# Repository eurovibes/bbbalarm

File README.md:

<!-- SPDX-FileCopyrightText: 2021 Benedikt Spranger <b.spranger@linutronix.de> -->
<!-- SPDX-License-Identifier: CERN-OHL-S-2.0 -->

# bbbalarm - An Alarm cape for Beaglebone Black

The Beaglobone Black is a TI Sitara AM3359 ARM Cortex-A8 CPU based
evaluation board with two 40pin 100mil pinsockets. These pinsockets
can be used for additional functionality boards called capes.
The bbbalarm cape enhance the Beaglebone Black by adding coupled and
decoupled inputs, that can be used to supervise an air condition or read out
a presence detector.

## License rules

bbbalarm is provided under the terms of the CERN-OHL-S license version 2 as
provided in the LICENSES/CERN-OHL-S-2.0 file.

Instead of adding license boilerplates to the individual files, bbbalarm uses
SPDX license identifiers, which are machine parseable and considered legaly
equivalent.

The SPDX license identifier in bbbalarm shall be added at the first possible
line in a file which can contain a comment. This is normally the first line
except for scripts. Scripts require the #!PATH_TO_INTERPRETER tag in the
first line; place the SPDX identifier into the second line.

The SPDX license identifier is added in form of a comment.

## Copyright and License

Copyright Benedikt Spranger 2021.
This source describes Open Hardware and is licensed under the CERNOHL-S v2.
You may redistribute and modify this source and make products using it
under the terms of the CERN-OHL-S v2
(https://ohwr.org/cern ohl s v2.txt ).
This source is distributed WITHOUT ANY EXPRESS OR IMPLIED
WARRANTY, INCLUDING OF MERCHANTABILITY, SATISFACTORY
QUALITY AND FITNESS FOR A PARTICULAR PURPOSE. Please see
the CERN-OHL-S v2 for applicable conditions.
Source location: https://github.com/eurovibes/bbbalarm
As per CERN-OHL-S v2 section 4, should You produce hardware based
on this source, You must where practicable maintain the Source Location
visible on the external case of the bbbalarm or other products you make using
this source.

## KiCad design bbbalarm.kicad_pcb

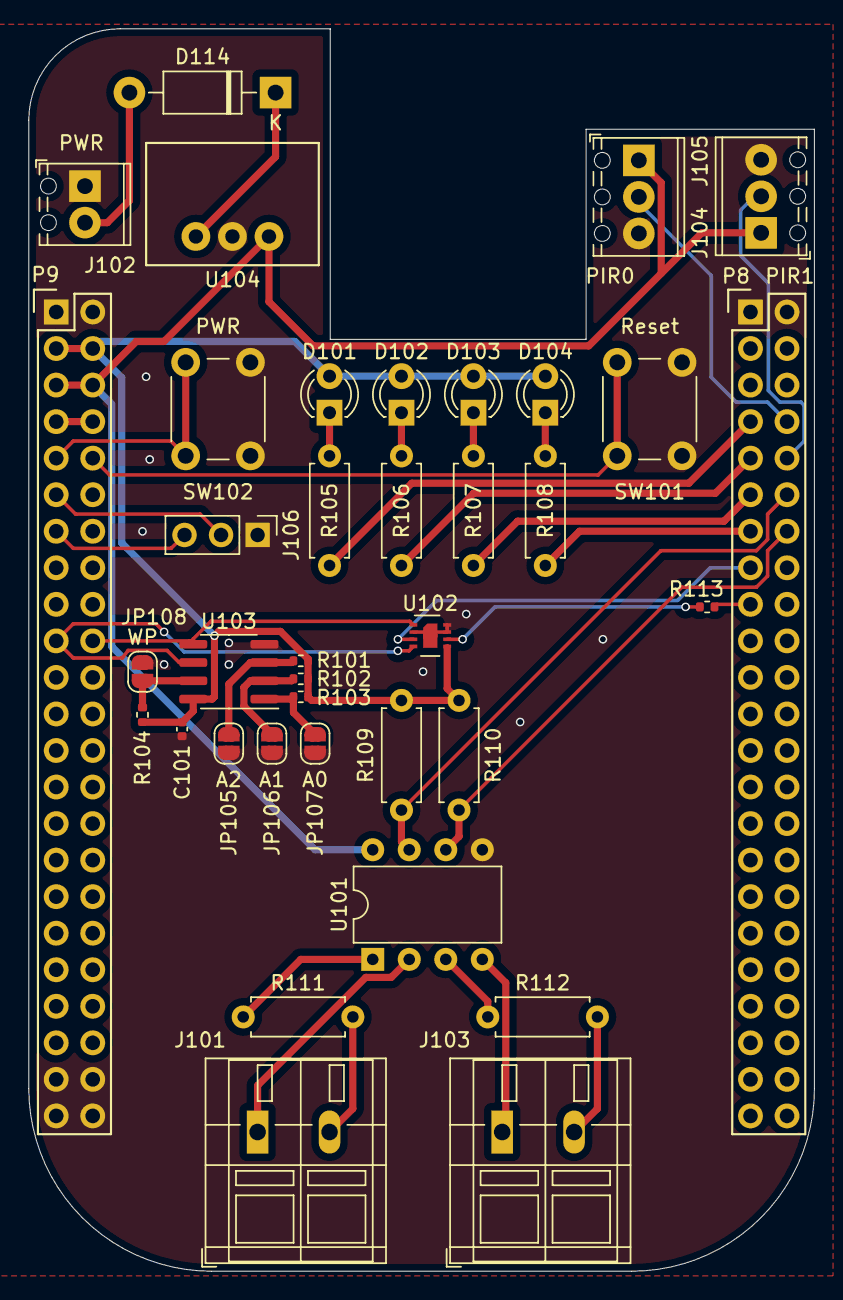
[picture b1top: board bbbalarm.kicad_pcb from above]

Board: 2 copper layers, 54.6 x 86.4 mm, 37 parts (0 on the bottom side), 37 nets.

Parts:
C101: 100n; C_0402_1005Metric
D101, D102, D103, D104: LED; LED_D3.0mm
D114: 1N4004; D_DO-41_SOD81_P10.16mm_Horizontal
J101: IN0; TerminalBlock_WAGO_236-102_1x02_P5.00mm_45Degree
J102: PWR; TerminalBlock_Phoenix_MPT-0,5-2-2.54_1x02_P2.54mm_Horizontal
J103: IN1; TerminalBlock_WAGO_236-102_1x02_P5.00mm_45Degree
J104: PIR0; TerminalBlock_Phoenix_MPT-0,5-3-2.54_1x03_P2.54mm_Horizontal
J105: PIR1; TerminalBlock_Phoenix_MPT-0,5-3-2.54_1x03_P2.54mm_Horizontal
J106: serial; PinHeader_1x03_P2.54mm_Vertical
JP105: A2; SolderJumper-2_P1.3mm_Open_RoundedPad1.0x1.5mm
JP106: A1; SolderJumper-2_P1.3mm_Open_RoundedPad1.0x1.5mm
JP107: A0; SolderJumper-2_P1.3mm_Open_RoundedPad1.0x1.5mm
JP108: WP; SolderJumper-2_P1.3mm_Open_RoundedPad1.0x1.5mm
P8, P9: BeagleBone_Black_Header; Socket_BeagleBone_Black
R101, R102, R103, R104, R113: 1k; R_0402_1005Metric
R105, R106, R107, R108, R109, R110: 1k; R_Axial_DIN0207_L6.3mm_D2.5mm_P7.62mm_Horizontal
R111, R112: 330; R_Axial_DIN0207_L6.3mm_D2.5mm_P7.62mm_Horizontal
SW101: Reset; SW_PUSH_6mm
SW102: PWR; SW_PUSH_6mm
U101: HCPL-263N; DIP-8_W7.62mm
U102: SHT35-DIS; Sensirion_DFN-8-1EP_2.5x2.5mm_P0.5mm_EP1.1x1.7mm
U103: AT24C512C-SSHD-T; SOIC-8_3.9x4.9mm_P1.27mm
U104: WPMDH1100xx1S

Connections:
+3V3: C101.1, D101.2 (A), D102.2 (A), D103.2 (A), D104.2 (A), P9.3, P9.4, R101.1, R102.1, R103.1, R104.1, R109.1, R110.1, U102.5 (VDD), U103.8 (VCC)
+5V: J104.1, J105.1, P9.5, P9.6, U101.8 (VCC), U104.3 (Vout)
/ALERT: P8.15, U102.3 (ALERT)
/IN0: P8.12, R109.2, U101.7 (VO1)
/IN1: P8.14, R110.2, U101.6 (VO2)
/LED0: P8.7, R105.2
/LED1: P8.9, R106.2
/LED2: P8.11, R107.2
/LED3: P8.13, R108.2
/PIR0: J104.2, P8.8
/PIR1: J105.2, P8.10
/RX: J106.2, P9.11
/SCL: P9.19, U102.4 (SCL), U103.6 (SCL)
/SDA: P9.20, U102.1 (SDA), U103.5 (SDA)
/TX: J106.3, P9.13
/nRST: P8.17, R113.1
GNDD: C101.2, J102.1, J104.3, J105.3, J106.1, JP105.2 (B), JP106.2 (B), JP107.2 (B), JP108.2 (B), P8.1, P8.2, P9.1, P9.2, P9.43, P9.44, P9.45, P9.46, SW101.2, SW102.2, U101.5 (GND), U102.2 (ADDR), U102.7 (R), U102.8 (VSS), U102.9 (VSS), U103.4 (GND), U104.2 (GND)
unnamed: D101.1 (K), R105.1
unnamed: D102.1 (K), R106.1
unnamed: D103.1 (K), R107.1
unnamed: D104.1 (K), R108.1
unnamed: D114.1 (K), U104.1 (Vin)
unnamed: D114.2 (A), J102.2
unnamed: J101.1, U101.2 (C1)
unnamed: J101.2, R111.2
unnamed: J103.1, U101.4 (A2)
unnamed: J103.2, R112.2
unnamed: JP105.1 (A), R101.2, U103.3 (A2)
unnamed: JP106.1 (A), R102.2, U103.2 (A1)
unnamed: JP107.1 (A), R103.2, U103.1 (A0)
unnamed: JP108.1 (A), R104.2, U103.7 (WP)
unnamed: R111.1, U101.1 (A1)
unnamed: R112.1, U101.3 (C2)
unnamed: R113.2, U102.6 (~RESET)
PWR_BUT: P9.9, SW102.1
SYS_5V: P9.7, P9.8
SYS_RESETN: P9.10, SW101.1

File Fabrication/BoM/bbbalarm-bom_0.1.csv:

Row,Referencias,Parte,Valor,P/N,Fabricante,Cod. Digi-Key,Footprint,Descripción,Quantity Per PCB
1,C101,C,100 nF,,,,C_0402_1005Metric,,1
2,D114,1N4004,1N4004,,,,D_DO-41_SOD81_P10.16mm_Horizontal,,1
3,D101 D102 D103 D104,LED,LED,,,,LED_D3.0mm,,4
4,J101 J102 J103,Conn_01x02,IN0,,,,TerminalBlock_WAGO_236-102_1x02_P5.00mm_45Degree,,3
5,J104 J105,Conn_01x03,PIR0,,,,"TerminalBlock_Phoenix_MPT-0,5-3-2.54_1x03_P2.54mm_Horizontal",,2
6,JP105 JP106 JP107 JP108,Jumper_NO_Small,A2,,,,SolderJumper-2_P1.3mm_Open_RoundedPad1.0x1.5mm,,4
7,P8 P9,Conn_02x23_Odd_Even,BeagleBone_Black_Header,,,,Socket_BeagleBone_Black,,2
8,R101 R102 R103 R104 R105 R106 R107 R108 R109 R110 R111 R112,R,1 kΩ,,,,R_0402_1005Metric,,12
9,SW101 SW102,SW_Push_45deg,Reset,,,,SW_PUSH_6mm,,2
10,U103,AT24CS64-SSHM,AT24C512C-SSHD-T,,,,SOIC-8_3.9x4.9mm_P1.27mm,,1
11,U101,HCPL-263N,HCPL-263N,,,,DIP-8_W7.62mm,,1
12,U104,WPMDH1100xx1S,WPMDH1100xx1S,,,,WPMDH1100xx1S,,1





Project info:
Schematic:,bbbalarm
Variant:,default
Revision:,0.1
Date:,2021-06-13
KiCad Version:,5.1.9+dfsg1-1~bpo10+1
Statistics:
Component Groups:,12
Component Count:,34
Fitted Components:,34
Number of PCBs:,1
Total Components:,34

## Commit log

2021-07-04 Deploying to gh-pages from @ eurovibes/bbbalarm@f948051098194ea80f819bb8f680f9af4a5954b1 🚀
2021-07-04 Initial gh page
    Add gh pages for project documentation.
2022-07-02 Update to KiCAD v6
2022-07-02 Add Temp sensor and serial header
2022-07-02 CI: Fix file permissions
2022-07-02 Deploying to gh-pages from @ eurovibes/bbbalarm@eebfd5ba7cbedf2e00b63c3b5749e4ad7ba35625 🚀
2022-07-02 CI: generate JLCPCB position file
2022-07-02 Fix typo in README
2022-07-02 CI: Rework HTML BOM
2022-07-02 Deploying to gh-pages from @ eurovibes/bbbalarm@3937efe38d74b34db45e0a4183c9bc5def640ca7 🚀
2022-07-02 Revisit Parts
2022-07-02 Deploying to gh-pages from @ eurovibes/bbbalarm@de7f87e87b92b0efb519c91df71b6fa631b74b0f 🚀
